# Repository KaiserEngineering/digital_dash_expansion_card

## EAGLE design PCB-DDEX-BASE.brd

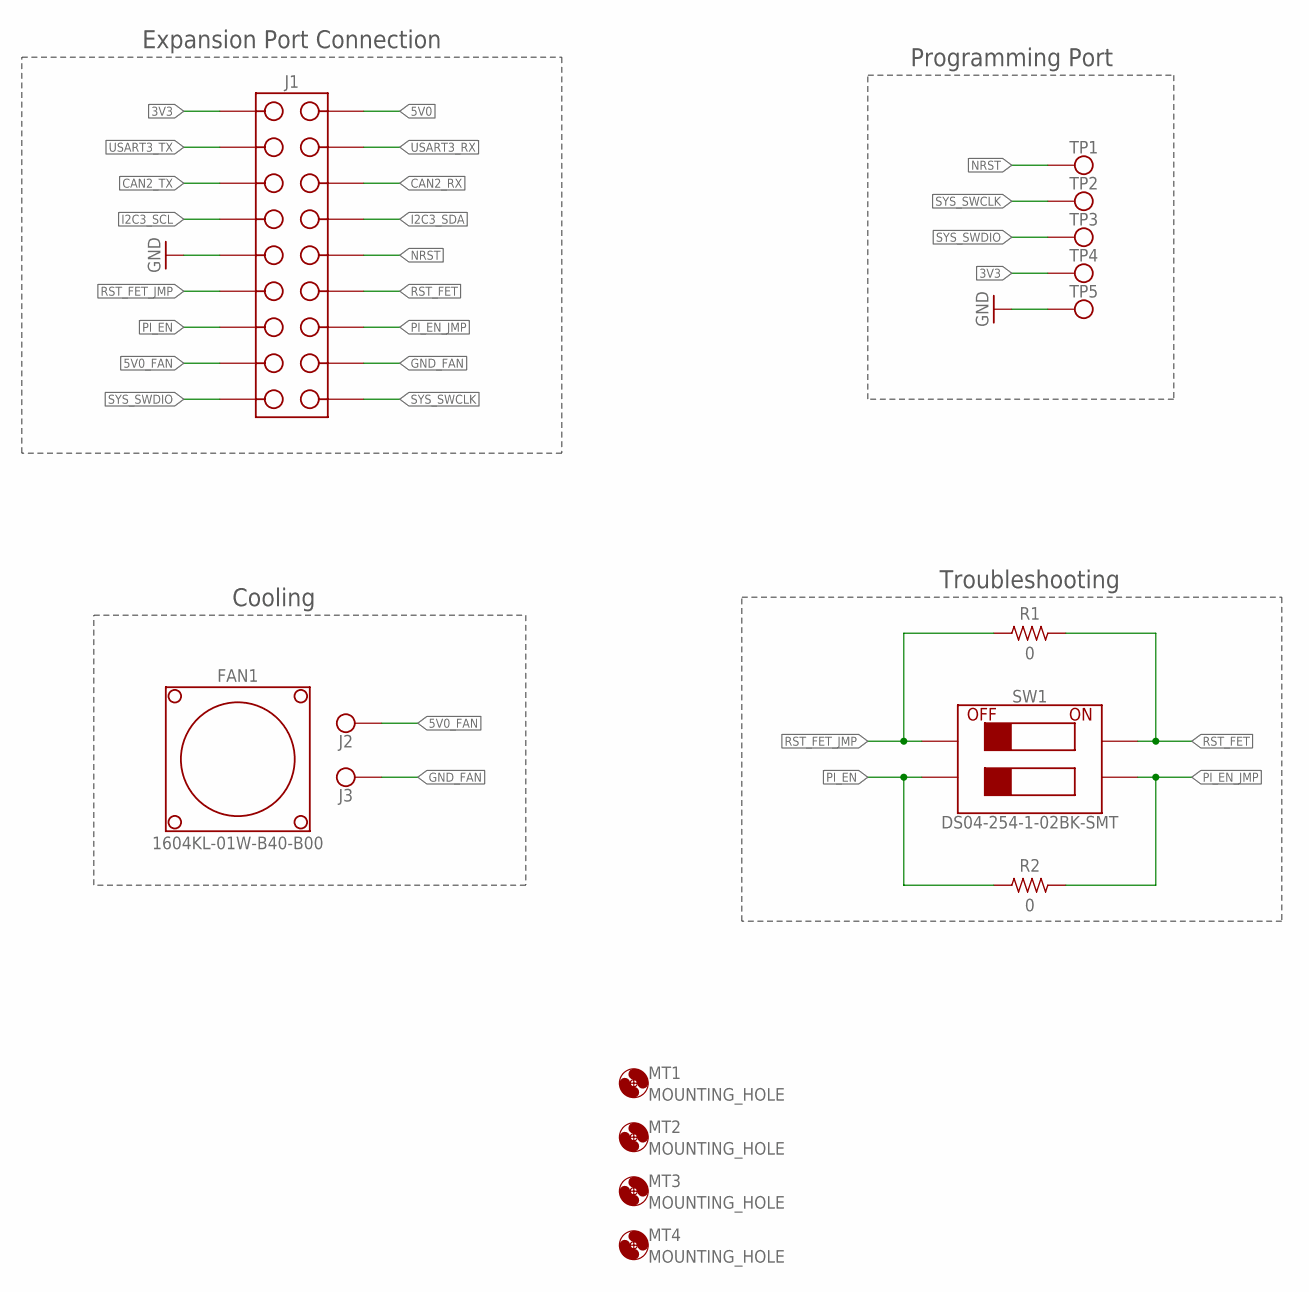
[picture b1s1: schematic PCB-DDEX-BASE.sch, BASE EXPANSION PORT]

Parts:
FAN1: NMB_1604KL-01W-B40-B00; NMB_40MMX40MMX10MM_FAN
J1: HEADER_9X2PIN_VERT; HEADER_100MIL_9X2
J2, J3: SOLDER_POINT; SMD_PAD_100X200
MT1, MT2, MT3, MT4: MOUNTING_HOLE; MT_2MM
R1, R2: 0; REST-0603
SW1: DIP2_CUI_DS04-254-1-02BK-SMT; DIP2_SMD_254
TP1, TP2, TP3, TP4, TP5: SOLDER_POINT_ROUND; SMD_PAD_ROUND

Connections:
3V3: J1.P$10 (10), TP4.1
5V0: J1.P$1 (1)
5V0_FAN: J1.P$17 (17), J2.1
CAN2_RX: J1.P$3 (3)
CAN2_TX: J1.P$12 (12)
GND: J1.P$14 (14), TP5.1
GND_FAN: J1.P$8 (8), J3.1
I2C3_SCL: J1.P$13 (13)
I2C3_SDA: J1.P$4 (4)
NRST: J1.P$5 (5), TP1.1
PI_EN: J1.P$16 (16), R2.1, SW1.3
PI_EN_JMP: J1.P$7 (7), R2.2, SW1.4
RST_FET: J1.P$6 (6), R1.2, SW1.2
RST_FET_JMP: J1.P$15 (15), R1.1, SW1.1
SYS_SWCLK: J1.P$9 (9), TP2.1
SYS_SWDIO: J1.P$18 (18), TP3.1
USART3_RX: J1.P$2 (2)
USART3_TX: J1.P$11 (11)

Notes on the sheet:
Cooling
Troubleshooting
Expansion Port Connection
Programming Port

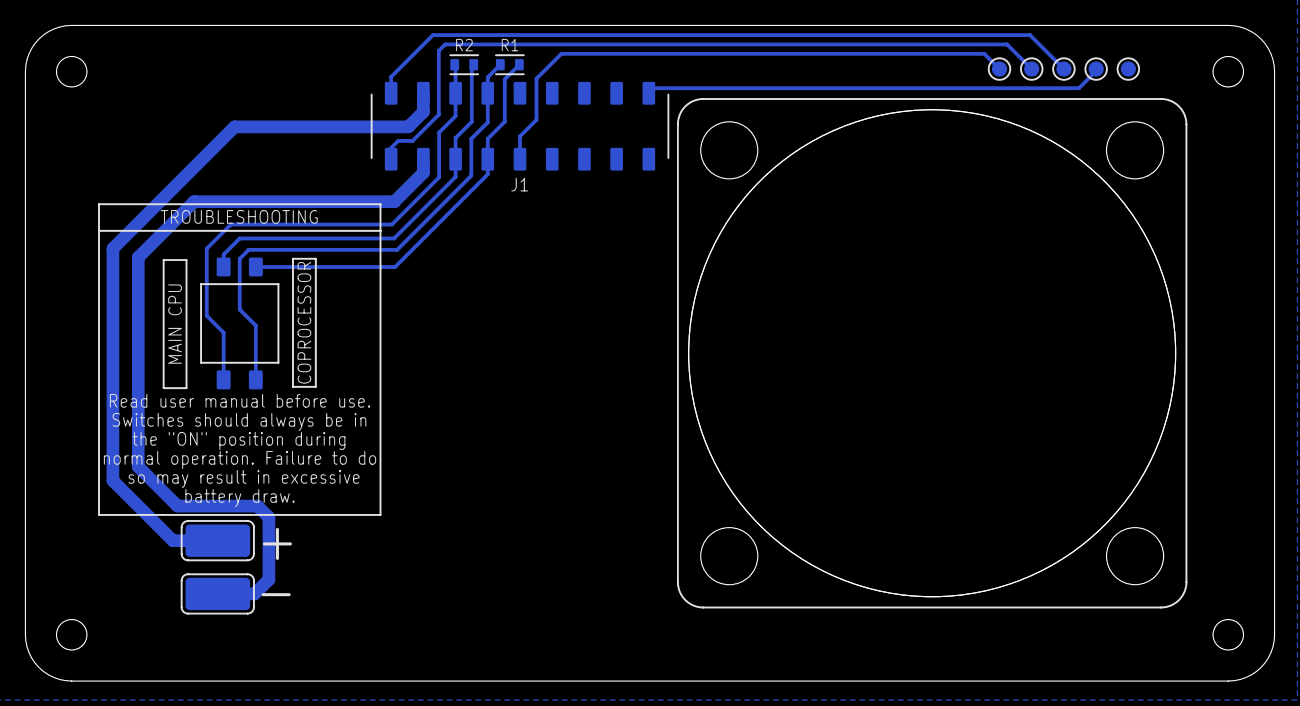
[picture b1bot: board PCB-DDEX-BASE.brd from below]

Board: 2 copper layers, 98.5 x 51.7 mm, 16 parts (12 on the bottom side), 11 nets.

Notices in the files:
PCB-DDEX-BASE.brd:
Copyright 2020
